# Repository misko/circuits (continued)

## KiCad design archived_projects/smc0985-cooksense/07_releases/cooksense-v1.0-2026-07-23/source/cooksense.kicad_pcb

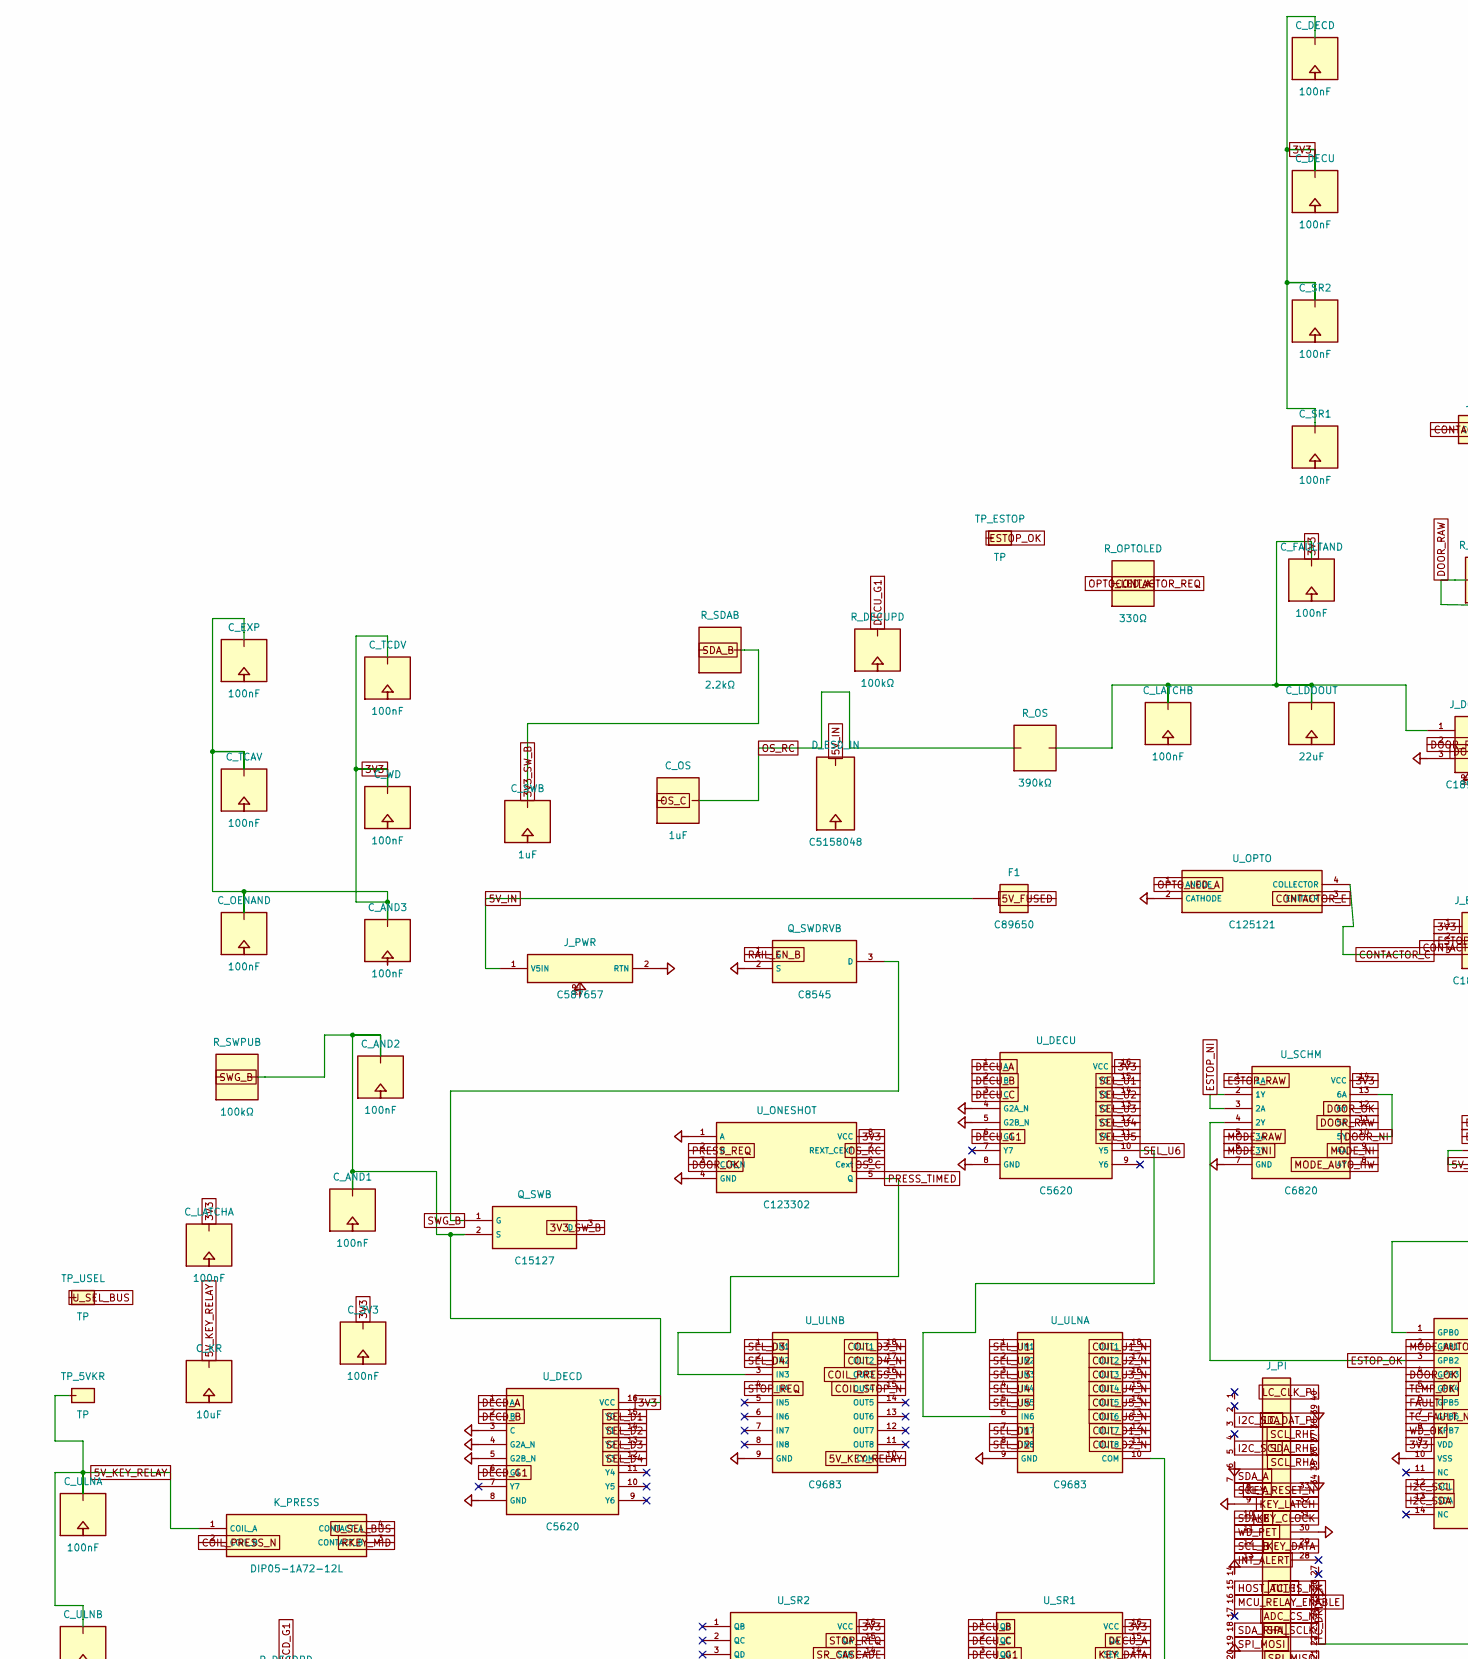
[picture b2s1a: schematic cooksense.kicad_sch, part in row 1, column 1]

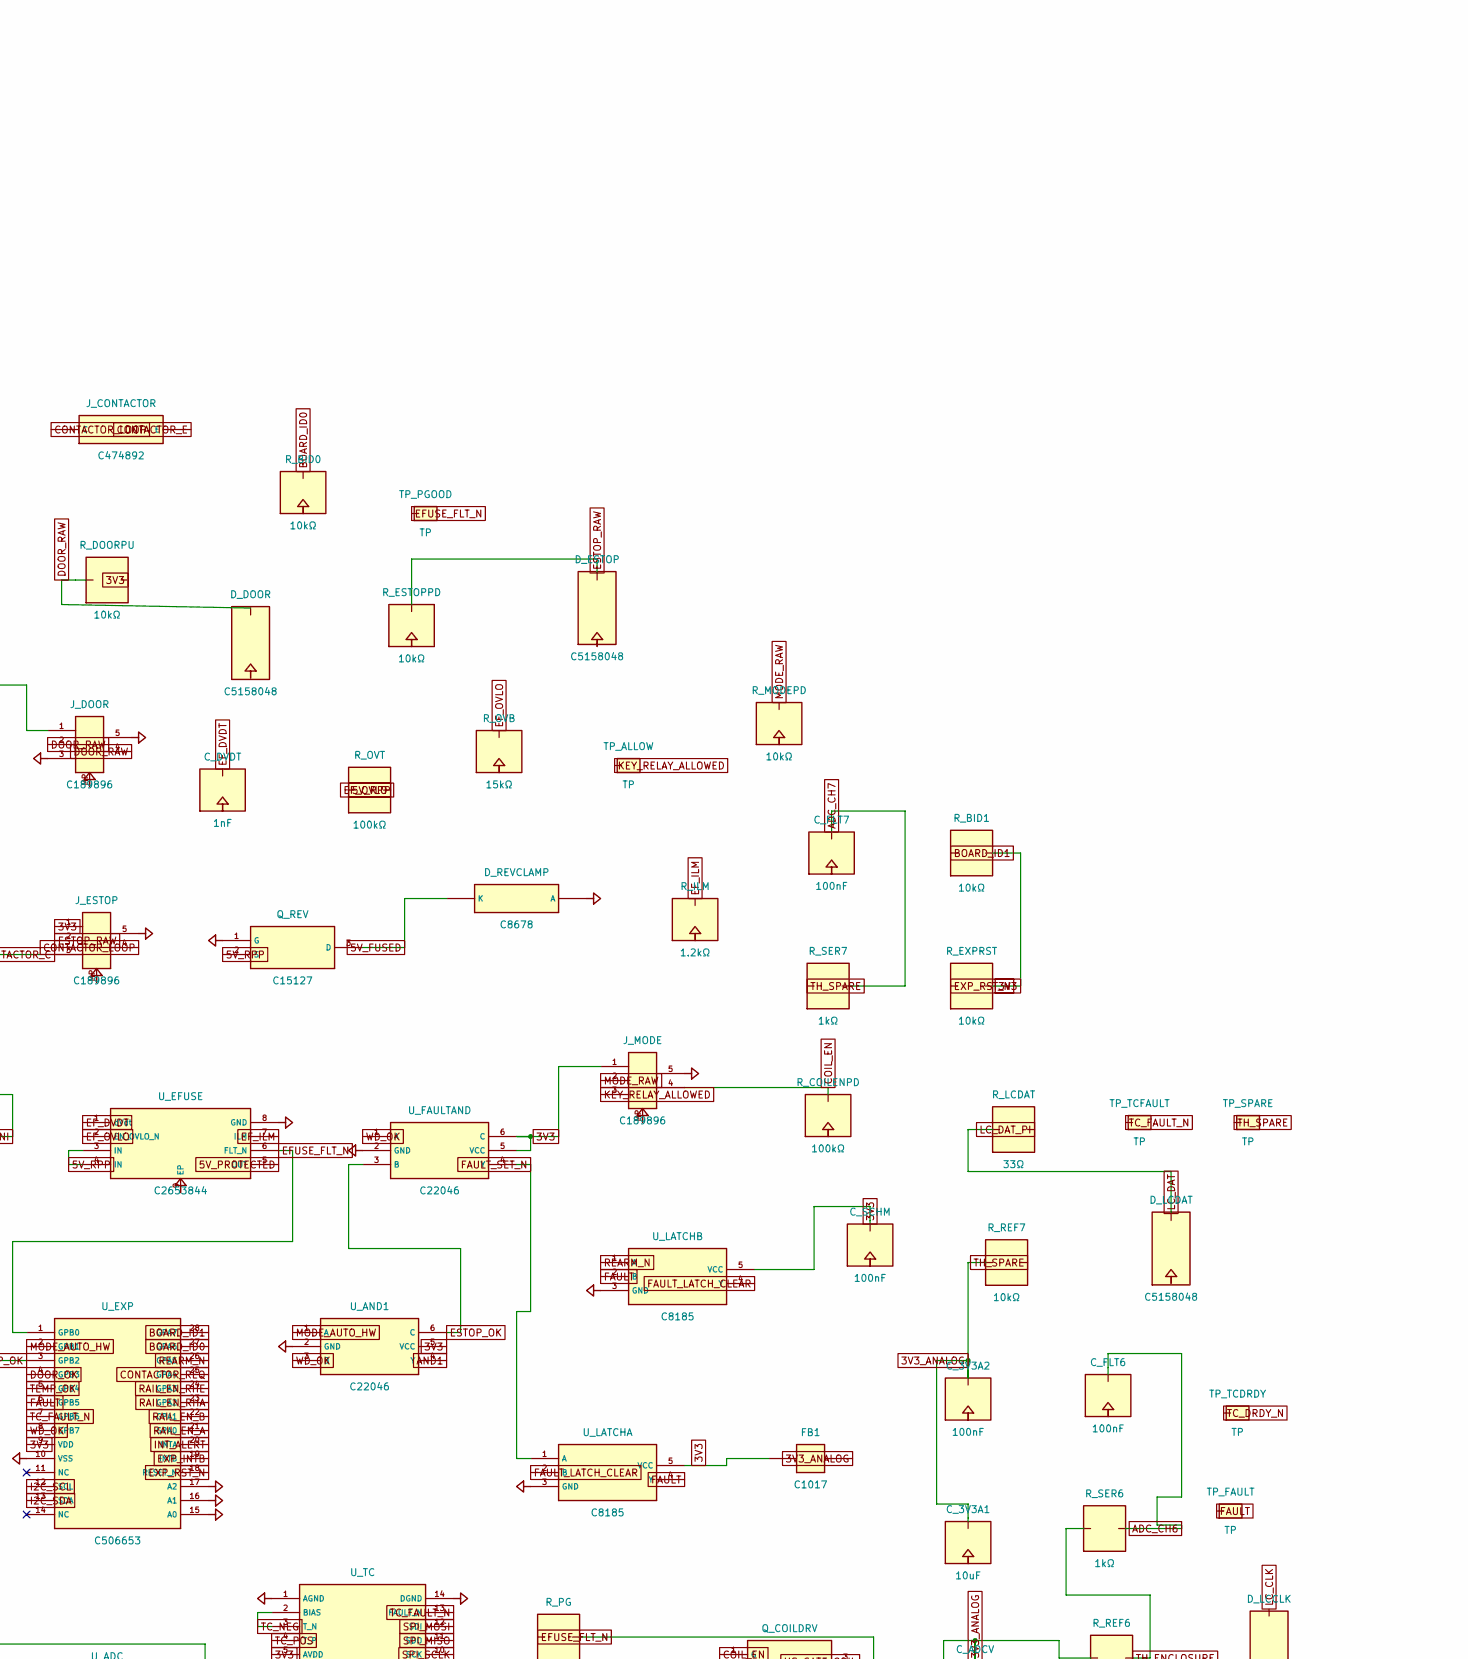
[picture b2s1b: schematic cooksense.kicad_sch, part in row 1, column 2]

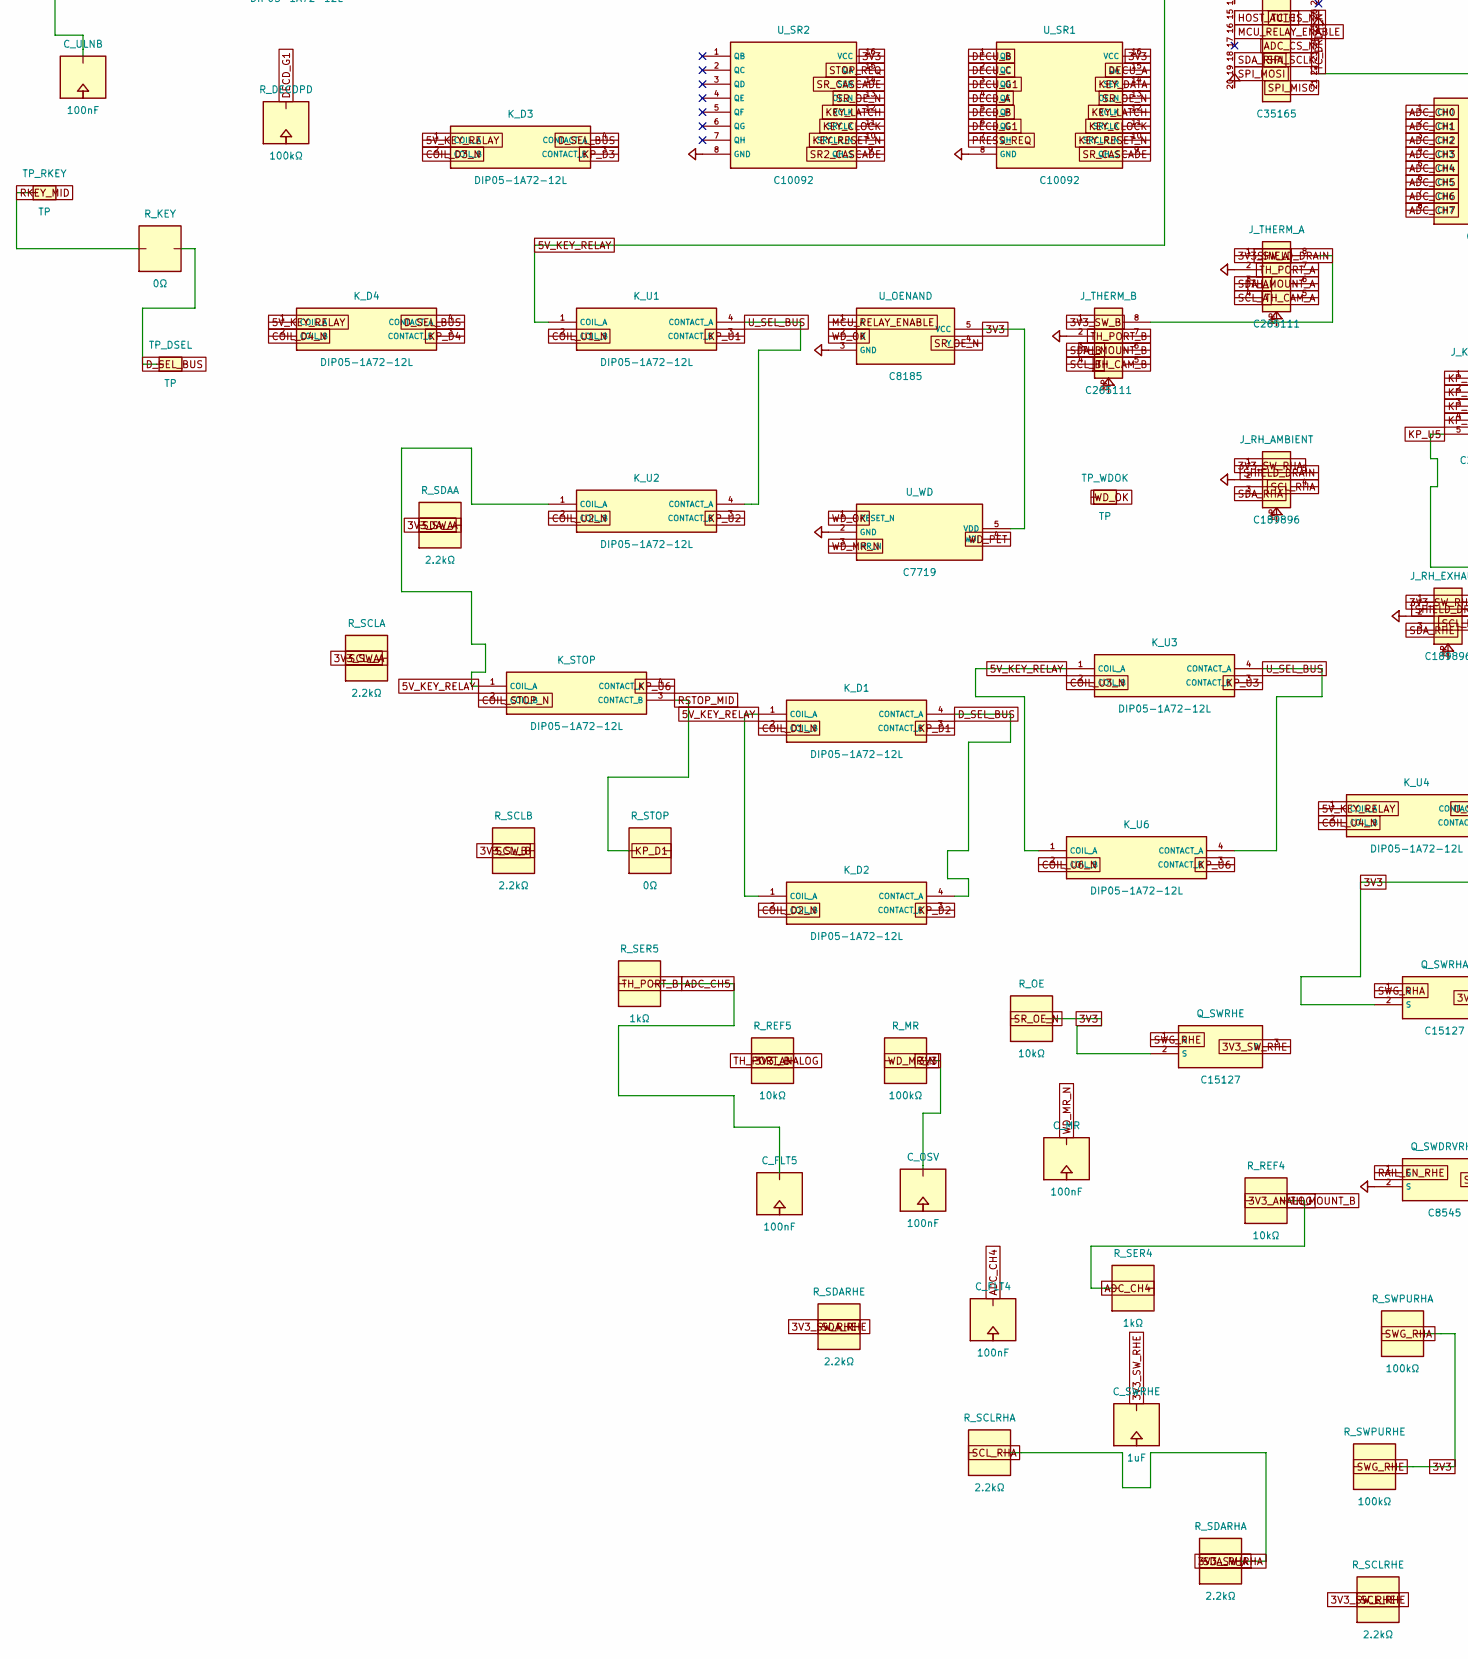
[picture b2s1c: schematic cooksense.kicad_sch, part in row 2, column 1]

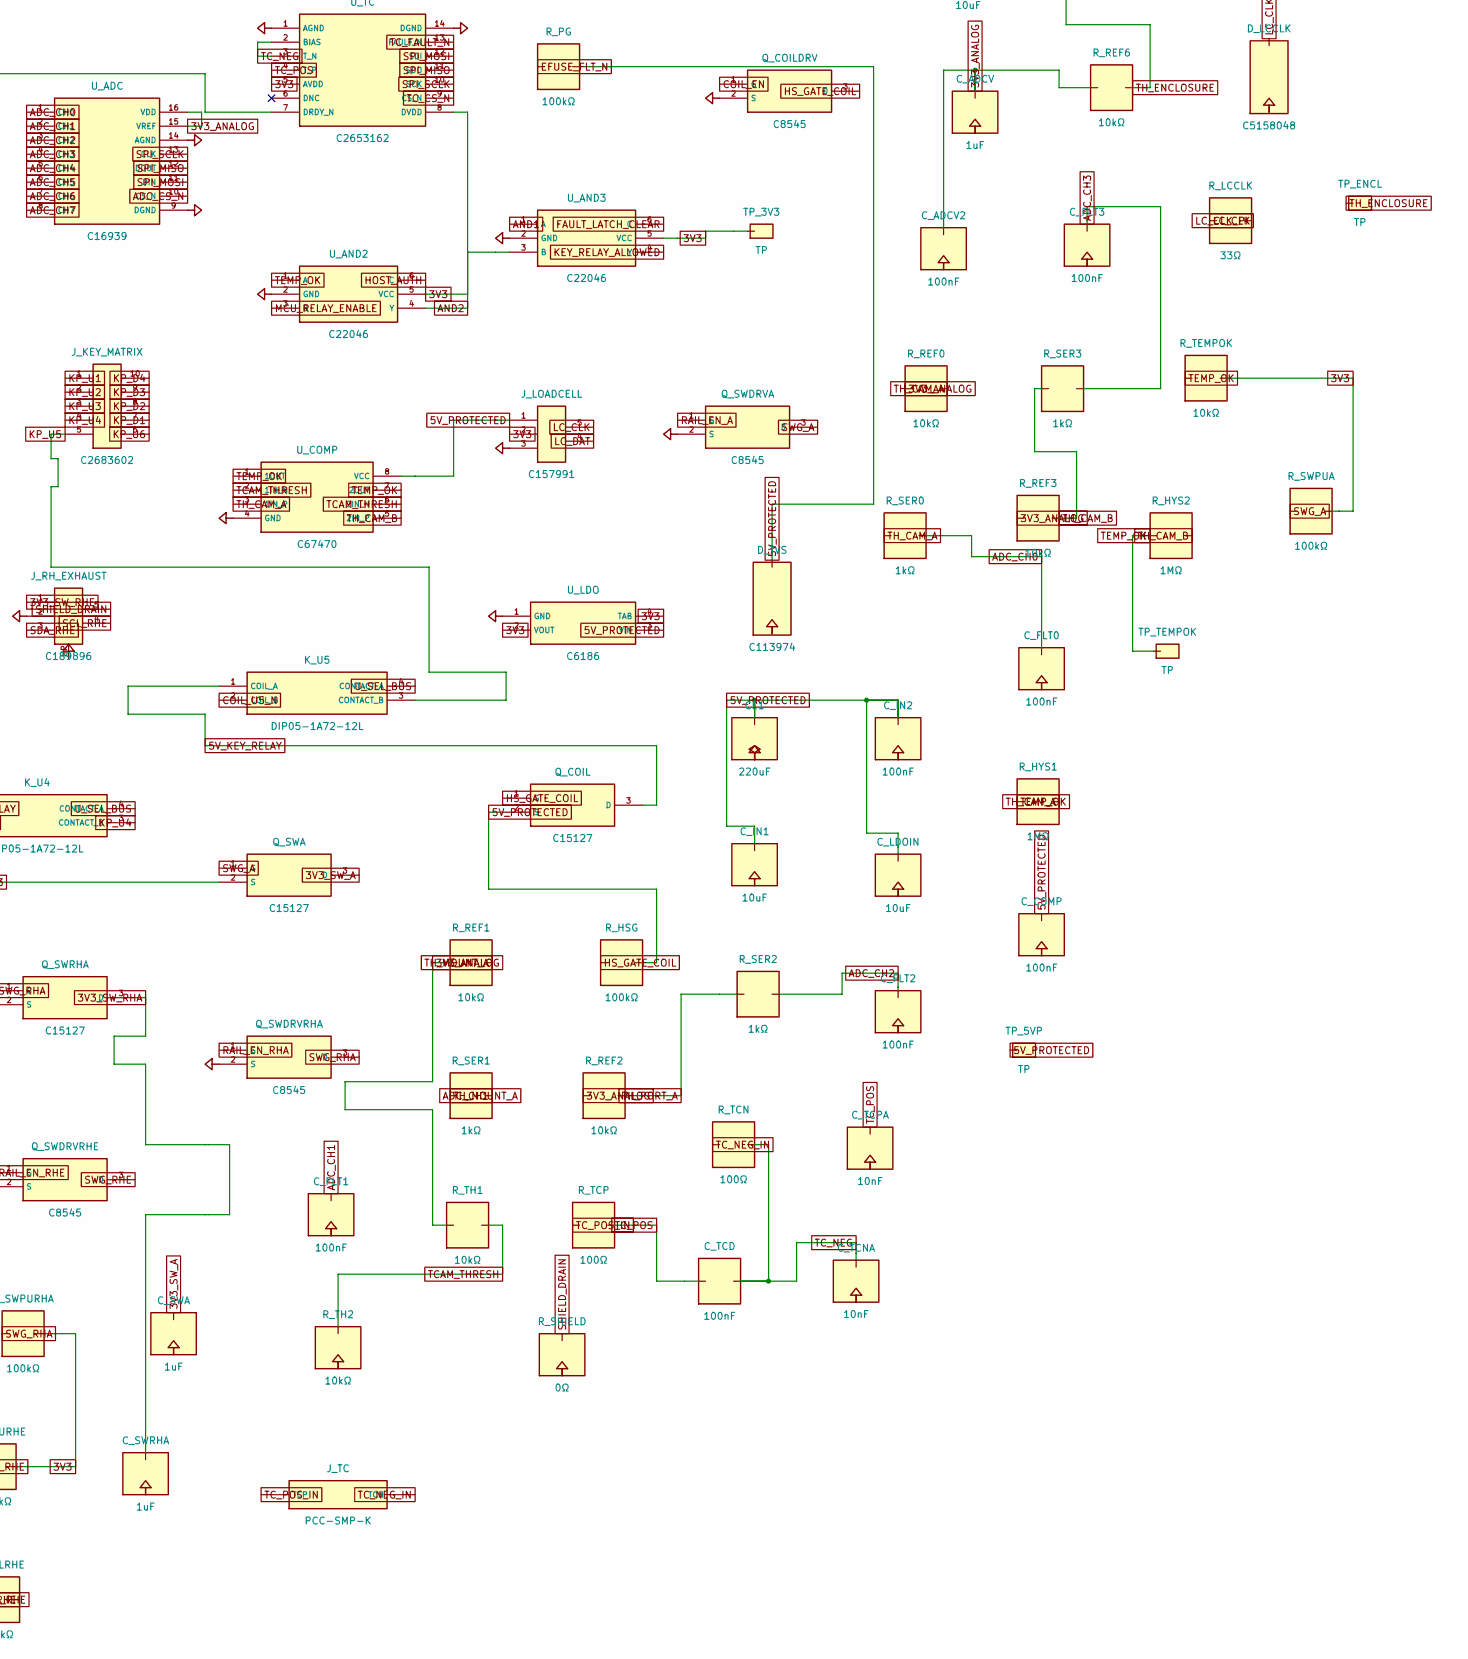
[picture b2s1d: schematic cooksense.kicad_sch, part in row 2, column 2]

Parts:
CE1: 220uF; CP_Elec_6.3x7.7
C_3V3, C_3V3A2: 100nF; C_0603_1608Metric
C_3V3A1: 10uF; C_0805_2012Metric
C_ADCV: 1uF; C_0603_1608Metric
C_ADCV2: 100nF; C_0402_1005Metric
C_AND1, C_AND2, C_AND3: 100nF; C_0402_1005Metric
C_COMP: 100nF; C_0402_1005Metric
C_DECD: 100nF; C_0402_1005Metric
C_DECU: 100nF; C_0402_1005Metric
C_DVDT: 1nF; C_0402_1005Metric
C_EXP: 100nF; C_0402_1005Metric
C_FAULTAND: 100nF; C_0402_1005Metric
C_FLT0, C_FLT1, C_FLT2, C_FLT3, C_FLT4, C_FLT5, C_FLT6, C_FLT7: 100nF; C_0402_1005Metric
C_IN1: 10uF; C_0805_2012Metric
C_IN2: 100nF; C_0603_1608Metric
C_KR: 10uF; C_0805_2012Metric
C_LATCHA: 100nF; C_0402_1005Metric
C_LATCHB: 100nF; C_0402_1005Metric
C_LDOIN: 10uF; C_0805_2012Metric
C_LDOOUT: 22uF; C_0805_2012Metric
C_MR: 100nF; C_0402_1005Metric
C_OENAND: 100nF; C_0402_1005Metric
C_OS: 1uF; C_0603_1608Metric
C_OSV: 100nF; C_0402_1005Metric
C_SCHM: 100nF; C_0402_1005Metric
C_SR1, C_SR2: 100nF; C_0402_1005Metric
C_SWA: 1uF; C_0603_1608Metric
C_SWB: 1uF; C_0603_1608Metric
C_SWRHA: 1uF; C_0603_1608Metric
C_SWRHE: 1uF; C_0603_1608Metric
C_TCAV: 100nF; C_0402_1005Metric
C_TCD: 100nF; C_0402_1005Metric
C_TCDV: 100nF; C_0402_1005Metric
C_TCNA: 10nF; C_0402_1005Metric
C_TCPA: 10nF; C_0402_1005Metric
C_ULNA: 100nF; C_0603_1608Metric
C_ULNB: 100nF; C_0603_1608Metric
C_WD: 100nF; C_0402_1005Metric
D_DOOR: C5158048; D_SOD-323
D_ESD_IN: C5158048; D_SOD-323
D_ESTOP: C5158048; D_SOD-323
D_LCCLK: C5158048; D_SOD-323
D_LCDAT: C5158048; D_SOD-323
D_REVCLAMP: C8678; D_SMA
D_TVS: C113974; D_SMB
F1: C89650; Fuse_1812_4532Metric
FB1: C1017; L_0805_2012Metric
J_CONTACTOR: C474892; TerminalBlock_KF350_2P
J_DOOR: C189896; JST_GH_SM05B-GHS-TB_1x05-1MP_P1.25mm_Horizontal
J_ESTOP: C189896; JST_GH_SM05B-GHS-TB_1x05-1MP_P1.25mm_Horizontal
J_KEY_MATRIX: C2683602; JST_GH_SM10B-GHS-TB_1x10-1MP_P1.25mm_Horizontal
J_LOADCELL: C157991; JST_XH_B5B-XH-A_1x05_P2.50mm_Vertical
J_MODE: C189896; JST_GH_SM05B-GHS-TB_1x05-1MP_P1.25mm_Horizontal
J_PI: C35165; PinSocket_2x20_P2.54mm_Vertical
J_PWR: C587657; Molex_Micro-Fit_3.0_43650-0224_1x02-1MP_P3.00mm_Vertical
J_RH_AMBIENT: C189896; JST_GH_SM05B-GHS-TB_1x05-1MP_P1.25mm_Horizontal
J_RH_EXHAUST: C189896; JST_GH_SM05B-GHS-TB_1x05-1MP_P1.25mm_Horizontal
J_TC: PCC-SMP-K; Omega_PCC-SMP-K_TypeK_PCpin
J_THERM_A: C265111; JST_GH_SM08B-GHS-TB_1x08-1MP_P1.25mm_Horizontal
J_THERM_B: C265111; JST_GH_SM08B-GHS-TB_1x08-1MP_P1.25mm_Horizontal
K_D1, K_D2, K_D3, K_D4: DIP05-1A72-12L; Relay_StandexDIP_1A_pinout12
K_PRESS: DIP05-1A72-12L; Relay_StandexDIP_1A_pinout12
K_STOP: DIP05-1A72-12L; Relay_StandexDIP_1A_pinout12
K_U1, K_U2, K_U3, K_U4, K_U5, K_U6: DIP05-1A72-12L; Relay_StandexDIP_1A_pinout12
Q_COIL: C15127; SOT-23
Q_COILDRV: C8545; SOT-23
Q_REV: C15127; SOT-23
Q_SWA: C15127; SOT-23
Q_SWB: C15127; SOT-23
Q_SWDRVA: C8545; SOT-23
Q_SWDRVB: C8545; SOT-23
Q_SWDRVRHA: C8545; SOT-23
Q_SWDRVRHE: C8545; SOT-23
Q_SWRHA: C15127; SOT-23
Q_SWRHE: C15127; SOT-23
R_BID0, R_BID1: 10kΩ; R_0402_1005Metric
R_COILENPD: 100kΩ; R_0402_1005Metric
R_DECDPD: 100kΩ; R_0402_1005Metric
R_DECUPD: 100kΩ; R_0402_1005Metric
R_DOORPU: 10kΩ; R_0402_1005Metric
R_ESTOPPD: 10kΩ; R_0402_1005Metric
R_EXPRST: 10kΩ; R_0402_1005Metric
R_HSG: 100kΩ; R_0402_1005Metric
R_HYS1, R_HYS2: 1MΩ; R_0402_1005Metric
R_ILM: 1.2kΩ; R_0402_1005Metric
R_KEY: 0Ω; R_1206_3216Metric
R_LCCLK: 33Ω; R_0402_1005Metric
R_LCDAT: 33Ω; R_0402_1005Metric
R_MODEPD: 10kΩ; R_0402_1005Metric
R_MR: 100kΩ; R_0402_1005Metric
R_OE: 10kΩ; R_0402_1005Metric
R_OPTOLED: 330Ω; R_0603_1608Metric
R_OS: 390kΩ; R_0402_1005Metric
R_OVB: 15kΩ; R_0402_1005Metric
R_OVT: 100kΩ; R_0402_1005Metric
R_PG: 100kΩ; R_0402_1005Metric
R_REF0, R_REF1, R_REF2, R_REF3, R_REF4, R_REF5, R_REF6, R_REF7: 10kΩ; R_0402_1005Metric
R_SCLA: 2.2kΩ; R_0402_1005Metric
R_SCLB: 2.2kΩ; R_0402_1005Metric
R_SCLRHA: 2.2kΩ; R_0402_1005Metric
R_SCLRHE: 2.2kΩ; R_0402_1005Metric
R_SDAA: 2.2kΩ; R_0402_1005Metric
R_SDAB: 2.2kΩ; R_0402_1005Metric
R_SDARHA: 2.2kΩ; R_0402_1005Metric
R_SDARHE: 2.2kΩ; R_0402_1005Metric
R_SER0, R_SER1, R_SER2, R_SER3, R_SER4, R_SER5, R_SER6, R_SER7: 1kΩ; R_0402_1005Metric
R_SHIELD: 0Ω; R_0603_1608Metric
R_STOP: 0Ω; R_1206_3216Metric
R_SWPUA: 100kΩ; R_0402_1005Metric
R_SWPUB: 100kΩ; R_0402_1005Metric
R_SWPURHA: 100kΩ; R_0402_1005Metric
R_SWPURHE: 100kΩ; R_0402_1005Metric
R_TCN: 100Ω; R_0402_1005Metric
R_TCP: 100Ω; R_0402_1005Metric
R_TEMPOK: 10kΩ; R_0402_1005Metric
R_TH1, R_TH2: 10kΩ; R_0402_1005Metric
TP_3V3, TP_5VKR, TP_5VP: TP; TestPoint_Pad_D1.5mm
TP_ALLOW: TP; TestPoint_Pad_D1.5mm
TP_DSEL: TP; TestPoint_Pad_D1.5mm
TP_ENCL: TP; TestPoint_Pad_D1.5mm
TP_ESTOP: TP; TestPoint_Pad_D1.5mm
TP_FAULT: TP; TestPoint_Pad_D1.5mm
TP_PGOOD: TP; TestPoint_Pad_D1.5mm
TP_RKEY: TP; TestPoint_Pad_D1.5mm
TP_SPARE: TP; TestPoint_Pad_D1.5mm
TP_TCDRDY: TP; TestPoint_Pad_D1.5mm
TP_TCFAULT: TP; TestPoint_Pad_D1.5mm
TP_TEMPOK: TP; TestPoint_Pad_D1.5mm
TP_USEL: TP; TestPoint_Pad_D1.5mm
TP_WDOK: TP; TestPoint_Pad_D1.5mm
U_ADC: C16939; SOIC-16_3.9x9.9mm_P1.27mm
U_AND1, U_AND2, U_AND3: C22046; SOT-23-6
U_COMP: C67470; SOIC-8_3.9x4.9mm_P1.27mm
U_DECD: C5620; SOIC-16_3.9x9.9mm_P1.27mm
U_DECU: C5620; SOIC-16_3.9x9.9mm_P1.27mm
U_EFUSE: C2653844; Texas_DSG0008A_WSON-8-1EP_2x2mm_P0.5mm_EP0.9x1.6mm
U_EXP: C506653; SSOP-28_5.3x10.2mm_P0.65mm
U_FAULTAND: C22046; SOT-23-6
U_LATCHA: C8185; SOT-353_SC-70-5
U_LATCHB: C8185; SOT-353_SC-70-5
U_LDO: C6186; SOT-223
U_OENAND: C8185; SOT-353_SC-70-5
U_ONESHOT: C123302; SSOP-8_2.95x2.8mm_P0.65mm
U_OPTO: C125121; SMDIP-4_W9.53mm
U_SCHM: C6820; SOIC-14_3.9x8.7mm_P1.27mm
U_SR1, U_SR2: C10092; SOIC-16_3.9x9.9mm_P1.27mm
U_TC: C2653162; TSSOP-14_4.4x5mm_P0.65mm
U_ULNA: C9683; SOIC-18W_7.5x11.6mm_P1.27mm
U_ULNB: C9683; SOIC-18W_7.5x11.6mm_P1.27mm
U_WD: C7719; SOT-23-5

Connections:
3V3: C_3V3.1, C_AND1.1, C_AND2.1, C_AND3.1, C_DECD.1, C_DECU.1, C_EXP.1, C_FAULTAND.1, C_LATCHA.1, C_LATCHB.1, C_LDOOUT.1, C_OENAND.1, C_OSV.1, C_SCHM.1, C_SR1.1, C_SR2.1, C_TCAV.1, C_TCDV.1, C_WD.1, FB1.1, J_DOOR.1, J_ESTOP.1, J_LOADCELL.2, J_MODE.1, Q_SWA.2 (S), Q_SWB.2 (S), Q_SWRHA.2 (S), Q_SWRHE.2 (S), R_BID1.2, R_DOORPU.2, R_EXPRST.2, R_MR.2, R_OE.2, R_OS.2, R_SWPUA.2, R_SWPUB.2, R_SWPURHA.2, R_SWPURHE.2, R_TEMPOK.2, TP_3V3.1, U_AND1.5 (VCC), U_AND2.5 (VCC), U_AND3.5 (VCC), U_DECD.16 (VCC), U_DECU.16 (VCC), U_EXP.9 (VDD), U_FAULTAND.5 (VCC), U_FAULTAND.6 (C), U_LATCHA.5 (VCC), U_LATCHB.5 (VCC), U_LDO.2 (VOUT), U_LDO.4 (TAB), U_OENAND.5 (VCC), U_ONESHOT.8 (VCC), U_SCHM.14 (VCC), U_SR1.16 (VCC), U_SR2.16 (VCC), U_TC.5 (AVDD), U_TC.8 (DVDD), U_WD.5 (VDD)
3V3_ANALOG: C_3V3A1.1, C_3V3A2.1, C_ADCV.1, C_ADCV2.1, FB1.2, R_REF0.1, R_REF1.1, R_REF2.1, R_REF3.1, R_REF4.1, R_REF5.1, R_REF6.1, R_REF7.1, R_TH1.1, U_ADC.15 (VREF), U_ADC.16 (VDD)
3V3_SW_A: C_SWA.1, J_THERM_A.1, Q_SWA.3 (D), R_SCLA.2, R_SDAA.2
3V3_SW_B: C_SWB.1, J_THERM_B.1, Q_SWB.3 (D), R_SCLB.2, R_SDAB.2
3V3_SW_RHA: C_SWRHA.1, J_RH_AMBIENT.1, Q_SWRHA.3 (D), R_SCLRHA.2, R_SDARHA.2
3V3_SW_RHE: C_SWRHE.1, J_RH_EXHAUST.1, Q_SWRHE.3 (D), R_SCLRHE.2, R_SDARHE.2
5V_FUSED: D_REVCLAMP.1 (K), F1.2, Q_REV.3 (D)
5V_IN: D_ESD_IN.1, F1.1, J_PWR.1 (V5IN)
5V_KEY_RELAY: C_KR.1, C_ULNA.1, C_ULNB.1, K_D1.1 (COIL_A), K_D2.1 (COIL_A), K_D3.1 (COIL_A), K_D4.1 (COIL_A), K_PRESS.1 (COIL_A), K_STOP.1 (COIL_A), K_U1.1 (COIL_A), K_U2.1 (COIL_A), K_U3.1 (COIL_A), K_U4.1 (COIL_A), K_U5.1 (COIL_A), K_U6.1 (COIL_A), Q_COIL.3 (D), TP_5VKR.1, U_ULNA.10 (COM), U_ULNB.10 (COM)
5V_PROTECTED: CE1.1, C_COMP.1, C_IN1.1, C_IN2.1, C_LDOIN.1, D_TVS.1, J_LOADCELL.1, Q_COIL.2 (S), R_HSG.2, R_PG.2, TP_5VP.1, U_COMP.8 (VCC), U_EFUSE.5 (OUT), U_LDO.3 (VIN)
5V_RPP: Q_REV.2 (S), R_OVT.1, U_EFUSE.3 (IN), U_EFUSE.4 (IN)
ADC_CH0: C_FLT0.1, R_SER0.2, U_ADC.1 (CH0)
ADC_CH1: C_FLT1.1, R_SER1.2, U_ADC.2 (CH1)
ADC_CH2: C_FLT2.1, R_SER2.2, U_ADC.3 (CH2)
ADC_CH3: C_FLT3.1, R_SER3.2, U_ADC.4 (CH3)
ADC_CH4: C_FLT4.1, R_SER4.2, U_ADC.5 (CH4)
ADC_CH5: C_FLT5.1, R_SER5.2, U_ADC.6 (CH5)
ADC_CH6: C_FLT6.1, R_SER6.2, U_ADC.7 (CH6)
ADC_CH7: C_FLT7.1, R_SER7.2, U_ADC.8 (CH7)
ADC_CS_N: J_PI.24, U_ADC.10 (CS_N)
AND1: U_AND1.4 (Y), U_AND3.1 (A)
AND2: U_AND2.4 (Y), U_AND3.3 (B)
BOARD_ID0: R_BID0.1, U_EXP.27 (GPA6)
BOARD_ID1: R_BID1.1, U_EXP.28 (GPA7)
COIL_D1_N: K_D1.2 (COIL_B), U_ULNA.12 (OUT7)
COIL_D2_N: K_D2.2 (COIL_B), U_ULNA.11 (OUT8)
COIL_D3_N: K_D3.2 (COIL_B), U_ULNB.18 (OUT1)
COIL_D4_N: K_D4.2 (COIL_B), U_ULNB.17 (OUT2)
COIL_EN: J_MODE.4, Q_COILDRV.1 (G), R_COILENPD.1
COIL_PRESS_N: K_PRESS.2 (COIL_B), U_ULNB.16 (OUT3)
COIL_STOP_N: K_STOP.2 (COIL_B), U_ULNB.15 (OUT4)
COIL_U1_N: K_U1.2 (COIL_B), U_ULNA.18 (OUT1)
COIL_U2_N: K_U2.2 (COIL_B), U_ULNA.17 (OUT2)
COIL_U3_N: K_U3.2 (COIL_B), U_ULNA.16 (OUT3)
COIL_U4_N: K_U4.2 (COIL_B), U_ULNA.15 (OUT4)
COIL_U5_N: K_U5.2 (COIL_B), U_ULNA.14 (OUT5)
COIL_U6_N: K_U6.2 (COIL_B), U_ULNA.13 (OUT6)
CONTACTOR_C: J_ESTOP.3, U_OPTO.4 (COLLECTOR)
CONTACTOR_E: J_CONTACTOR.2 (E), U_OPTO.3 (EMITTER)
CONTACTOR_LOOP: J_CONTACTOR.1 (C), J_ESTOP.4
CONTACTOR_REQ: R_OPTOLED.1, U_EXP.25 (GPA4)
DECD_A: U_DECD.1 (A), U_SR1.4 (QE)
DECD_B: U_DECD.2 (B), U_SR1.5 (QF)
DECD_G1: R_DECDPD.1, U_DECD.6 (G1), U_SR1.6 (QG)
DECU_A: U_DECU.1 (A), U_SR1.15 (QA)
DECU_B: U_DECU.2 (B), U_SR1.1 (QB)
DECU_C: U_DECU.3 (C), U_SR1.2 (QC)
DECU_G1: R_DECUPD.1, U_DECU.6 (G1), U_SR1.3 (QD)
DOOR_NI: U_SCHM.10 (5Y), U_SCHM.13 (6A)
DOOR_OK: U_EXP.4 (GPB3), U_ONESHOT.3 (CLR_N), U_SCHM.12 (6Y)
DOOR_RAW: D_DOOR.1, J_DOOR.2, J_DOOR.4, R_DOORPU.1, U_SCHM.11 (5A)
D_SEL_BUS: K_D1.4 (CONTACT_A), K_D2.4 (CONTACT_A), K_D3.4 (CONTACT_A), K_D4.4 (CONTACT_A), R_KEY.2, TP_DSEL.1
EFUSE_FLT_N: R_PG.1, TP_PGOOD.1, U_EFUSE.6 (FLT_N), U_EXP.1 (GPB0)
EF_DVDT: C_DVDT.1, U_EFUSE.1 (dVdt)
EF_ILM: R_ILM.1, U_EFUSE.7 (ILM)
EF_OVLO: R_OVB.1, R_OVT.2, U_EFUSE.2 (EN_OVLO_N)
ESTOP_NI: U_SCHM.2 (1Y), U_SCHM.3 (2A)
ESTOP_OK: TP_ESTOP.1, U_AND1.6 (C), U_EXP.3 (GPB2), U_FAULTAND.3 (B), U_SCHM.4 (2Y)
ESTOP_RAW: D_ESTOP.1, J_ESTOP.2, R_ESTOPPD.1, U_SCHM.1 (1A)
EXP_INTB: U_EXP.19 (INTB)
EXP_RST_N: R_EXPRST.1, U_EXP.18 (RESET_N)
FAULT: TP_FAULT.1, U_EXP.6 (GPB5), U_LATCHA.4 (Y), U_LATCHB.2 (B)
FAULT_LATCH_CLEAR: U_AND3.6 (C), U_LATCHA.2 (B), U_LATCHB.4 (Y)
FAULT_SET_N: U_FAULTAND.4 (Y), U_LATCHA.1 (A)
GND: CE1.2, C_3V3.2, C_3V3A1.2, C_3V3A2.2, C_ADCV.2, C_ADCV2.2, C_AND1.2, C_AND2.2, C_AND3.2, C_COMP.2, C_DECD.2, C_DECU.2, C_DVDT.2, C_EXP.2, C_FAULTAND.2, C_FLT0.2, C_FLT1.2, C_FLT2.2, C_FLT3.2, C_FLT4.2, C_FLT5.2, C_FLT6.2, C_FLT7.2, C_IN1.2, C_IN2.2, C_KR.2, C_LATCHA.2, C_LATCHB.2, C_LDOIN.2, C_LDOOUT.2, C_MR.2, C_OENAND.2, C_OSV.2, C_SCHM.2, C_SR1.2, C_SR2.2, C_SWA.2, C_SWB.2, C_SWRHA.2, C_SWRHE.2, C_TCAV.2, C_TCDV.2, C_TCNA.2, C_TCPA.2, C_ULNA.2, C_ULNB.2, C_WD.2, D_DOOR.2, D_ESD_IN.2, D_ESTOP.2, D_LCCLK.2, D_LCDAT.2, D_REVCLAMP.2 (A), D_TVS.2, J_DOOR.3, J_DOOR.5, J_DOOR.MP, J_ESTOP.5, J_ESTOP.MP, J_LOADCELL.3, J_MODE.5, J_MODE.MP, J_PI.6, J_PI.9, J_PI.14, J_PI.20, J_PI.25, J_PI.30, J_PI.34, J_PI.39, J_PWR.2 (RTN), J_PWR.MP, J_RH_AMBIENT.2, J_RH_AMBIENT.MP, J_RH_EXHAUST.2, J_RH_EXHAUST.MP, J_THERM_A.2, J_THERM_A.MP, J_THERM_B.2, J_THERM_B.MP, Q_COILDRV.2 (S), Q_REV.1 (G), Q_SWDRVA.2 (S), Q_SWDRVB.2 (S), Q_SWDRVRHA.2 (S), Q_SWDRVRHE.2 (S), R_BID0.2, R_COILENPD.2, R_DECDPD.2, R_DECUPD.2, R_ESTOPPD.2, R_ILM.2, R_MODEPD.2, R_OVB.2, R_SHIELD.2, R_TH2.2, U_ADC.9 (DGND), U_ADC.14 (AGND), U_AND1.2 (GND), U_AND2.2 (GND), U_AND3.2 (GND), U_COMP.4 (GND), U_DECD.3 (C), U_DECD.4 (G2A_N), U_DECD.5 (G2B_N), U_DECD.8 (GND), U_DECU.4 (G2A_N), U_DECU.5 (G2B_N), U_DECU.8 (GND), U_EFUSE.8 (GND), U_EFUSE.9 (EP), U_EXP.10 (VSS), U_EXP.15 (A0), U_EXP.16 (A1), U_EXP.17 (A2), U_FAULTAND.2 (GND), U_LATCHA.3 (GND), U_LATCHB.3 (GND), U_LDO.1 (GND), U_OENAND.3 (GND), U_ONESHOT.1 (A), U_ONESHOT.4 (GND), U_OPTO.2 (CATHODE), U_SCHM.7 (GND), U_SR1.8 (GND), U_SR2.8 (GND), U_TC.1 (AGND), U_TC.14 (DGND), U_ULNA.9 (GND), U_ULNB.9 (GND), U_WD.2 (GND)
HOST_AUTH: J_PI.15, U_AND2.6 (C)
HS_GATE_COIL: Q_COIL.1 (G), Q_COILDRV.3 (D), R_HSG.1
I2C_SCL: J_PI.5, U_EXP.12 (SCL)
I2C_SDA: J_PI.3, U_EXP.13 (SDA)
INT_ALERT: J_PI.13, U_EXP.20 (INTA)
KEY_CLOCK: J_PI.31, U_SR1.11 (SRCLK), U_SR2.11 (SRCLK)
KEY_DATA: J_PI.29, U_SR1.14 (SER)
KEY_LATCH: J_PI.32, U_SR1.12 (RCLK), U_SR2.12 (RCLK)
KEY_RELAY_ALLOWED: J_MODE.3, TP_ALLOW.1, U_AND3.4 (Y)
KEY_RESET_N: J_PI.33, U_SR1.10 (SRCLR_N), U_SR2.10 (SRCLR_N)
KP_D1: J_KEY_MATRIX.7, K_D1.3 (CONTACT_B), R_STOP.2
KP_D2: J_KEY_MATRIX.8, K_D2.3 (CONTACT_B)
KP_D3: J_KEY_MATRIX.9, K_D3.3 (CONTACT_B)
KP_D4: J_KEY_MATRIX.10, K_D4.3 (CONTACT_B)
KP_U1: J_KEY_MATRIX.1, K_U1.3 (CONTACT_B)
KP_U2: J_KEY_MATRIX.2, K_U2.3 (CONTACT_B)
KP_U3: J_KEY_MATRIX.3, K_U3.3 (CONTACT_B)
KP_U4: J_KEY_MATRIX.4, K_U4.3 (CONTACT_B)
KP_U5: J_KEY_MATRIX.5, K_U5.3 (CONTACT_B)
KP_U6: J_KEY_MATRIX.6, K_STOP.4 (CONTACT_A), K_U6.3 (CONTACT_B)
LC_CLK: D_LCCLK.1, J_LOADCELL.5, R_LCCLK.1
LC_CLK_PI: J_PI.40, R_LCCLK.2
LC_DAT: D_LCDAT.1, J_LOADCELL.4, R_LCDAT.1
LC_DAT_PI: J_PI.38, R_LCDAT.2
MCU_RELAY_ENABLE: J_PI.16, U_AND2.3 (B), U_OENAND.1 (A)
MODE_AUTO_HW: U_AND1.1 (A), U_EXP.2 (GPB1), U_SCHM.8 (4Y)
MODE_NI: U_SCHM.6 (3Y), U_SCHM.9 (4A)
MODE_RAW: J_MODE.2, R_MODEPD.1, U_SCHM.5 (3A)
OPTO_LED_A: R_OPTOLED.2, U_OPTO.1 (ANODE)
OS_C: C_OS.1, U_ONESHOT.6 (Cext)
OS_RC: C_OS.2, R_OS.1, U_ONESHOT.7 (REXT_CEXT)
PRESS_REQ: U_ONESHOT.2 (B), U_SR1.7 (QH)
PRESS_TIMED: U_ONESHOT.5 (Q), U_ULNB.3 (IN3)
RAIL_EN_A: Q_SWDRVA.1 (G), U_EXP.21 (GPA0)
RAIL_EN_B: Q_SWDRVB.1 (G), U_EXP.22 (GPA1)
RAIL_EN_RHA: Q_SWDRVRHA.1 (G), U_EXP.23 (GPA2)
RAIL_EN_RHE: Q_SWDRVRHE.1 (G), U_EXP.24 (GPA3)
REARM_N: U_EXP.26 (GPA5), U_LATCHB.1 (A)
RKEY_MID: K_PRESS.3 (CONTACT_B), R_KEY.1, TP_RKEY.1
RSTOP_MID: K_STOP.3 (CONTACT_B), R_STOP.1
SCL_A: J_PI.8, J_THERM_A.4, R_SCLA.1
SCL_B: J_PI.12, J_THERM_B.4, R_SCLB.1
SCL_RHA: J_PI.35, J_RH_AMBIENT.4, R_SCLRHA.1
SCL_RHE: J_PI.37, J_RH_EXHAUST.4, R_SCLRHE.1
SDA_A: J_PI.7, J_THERM_A.3, R_SDAA.1
SDA_B: J_PI.10, J_THERM_B.3, R_SDAB.1
SDA_RHA: J_PI.18, J_RH_AMBIENT.3, R_SDARHA.1
SDA_RHE: J_PI.36, J_RH_EXHAUST.3, R_SDARHE.1
SEL_D1: U_DECD.15 (Y0), U_ULNA.7 (IN7)
SEL_D2: U_DECD.14 (Y1), U_ULNA.8 (IN8)
SEL_D3: U_DECD.13 (Y2), U_ULNB.1 (IN1)
SEL_D4: U_DECD.12 (Y3), U_ULNB.2 (IN2)
SEL_U1: U_DECU.15 (Y0), U_ULNA.1 (IN1)
SEL_U2: U_DECU.14 (Y1), U_ULNA.2 (IN2)
SEL_U3: U_DECU.13 (Y2), U_ULNA.3 (IN3)
SEL_U4: U_DECU.12 (Y3), U_ULNA.4 (IN4)
SEL_U5: U_DECU.11 (Y4), U_ULNA.5 (IN5)
SEL_U6: U_DECU.10 (Y5), U_ULNA.6 (IN6)
SHIELD_DRAIN: J_RH_AMBIENT.5, J_RH_EXHAUST.5, J_THERM_A.8, J_THERM_B.8, R_SHIELD.1
SPI_MISO: J_PI.21, U_ADC.12 (DOUT), U_TC.11 (SDO)
SPI_MOSI: J_PI.19, U_ADC.11 (DIN), U_TC.12 (SDI)
SPI_SCLK: J_PI.23, U_ADC.13 (CLK), U_TC.10 (SCK)
SR2_CASCADE: U_SR2.9 (QH_S)
SR_CASCADE: U_SR1.9 (QH_S), U_SR2.14 (SER)
SR_OE_N: R_OE.1, U_OENAND.4 (Y), U_SR1.13 (OE_N), U_SR2.13 (OE_N)
STOP_REQ: U_SR2.15 (QA), U_ULNB.4 (IN4)
SWG_A: Q_SWA.1 (G), Q_SWDRVA.3 (D), R_SWPUA.1
SWG_B: Q_SWB.1 (G), Q_SWDRVB.3 (D), R_SWPUB.1
SWG_RHA: Q_SWDRVRHA.3 (D), Q_SWRHA.1 (G), R_SWPURHA.1
SWG_RHE: Q_SWDRVRHE.3 (D), Q_SWRHE.1 (G), R_SWPURHE.1
TCAM_THRESH: R_TH1.2, R_TH2.1, U_COMP.2 (1IN_N), U_COMP.6 (2IN_N)
TC_CS_N: J_PI.26, U_TC.9 (CS_N)
TC_DRDY_N: J_PI.22, TP_TCDRDY.1, U_TC.7 (DRDY_N)
TC_FAULT_N: TP_TCFAULT.1, U_EXP.7 (GPB6), U_TC.13 (FAULT_N)
TC_NEG: C_TCD.2, C_TCNA.1, R_TCN.2, U_TC.2 (BIAS), U_TC.3 (T_N)
TC_NEG_IN: J_TC.2 (TCN), R_TCN.1
TC_POS: C_TCD.1, C_TCPA.1, R_TCP.2, U_TC.4 (T_P)
TC_POS_IN: J_TC.1 (TCP), R_TCP.1
TEMP_OK: R_HYS1.1, R_HYS2.1, R_TEMPOK.1, TP_TEMPOK.1, U_AND2.1 (A), U_COMP.1 (1OUT), U_COMP.7 (2OUT), U_EXP.5 (GPB4)
TH_CAM_A: J_THERM_A.5, R_HYS1.2, R_REF0.2, R_SER0.1, U_COMP.3 (1IN_P)
TH_CAM_B: J_THERM_B.5, R_HYS2.2, R_REF3.2, R_SER3.1, U_COMP.5 (2IN_P)
TH_ENCLOSURE: R_REF6.2, R_SER6.1, TP_ENCL.1
TH_MOUNT_A: J_THERM_A.6, R_REF1.2, R_SER1.1
TH_MOUNT_B: J_THERM_B.6, R_REF4.2, R_SER4.1
TH_PORT_A: J_THERM_A.7, R_REF2.2, R_SER2.1
TH_PORT_B: J_THERM_B.7, R_REF5.2, R_SER5.1
TH_SPARE: R_REF7.2, R_SER7.1, TP_SPARE.1
U_SEL_BUS: K_PRESS.4 (CONTACT_A), K_U1.4 (CONTACT_A), K_U2.4 (CONTACT_A), K_U3.4 (CONTACT_A), K_U4.4 (CONTACT_A), K_U5.4 (CONTACT_A), K_U6.4 (CONTACT_A), TP_USEL.1
WD_MR_N: C_MR.1, R_MR.1, U_WD.3 (MR_N)
WD_OK: TP_WDOK.1, U_AND1.3 (B), U_EXP.8 (GPB7), U_FAULTAND.1 (A), U_OENAND.2 (B), U_WD.1 (RESET_N)
WD_PET: J_PI.11, U_WD.4 (WDI)

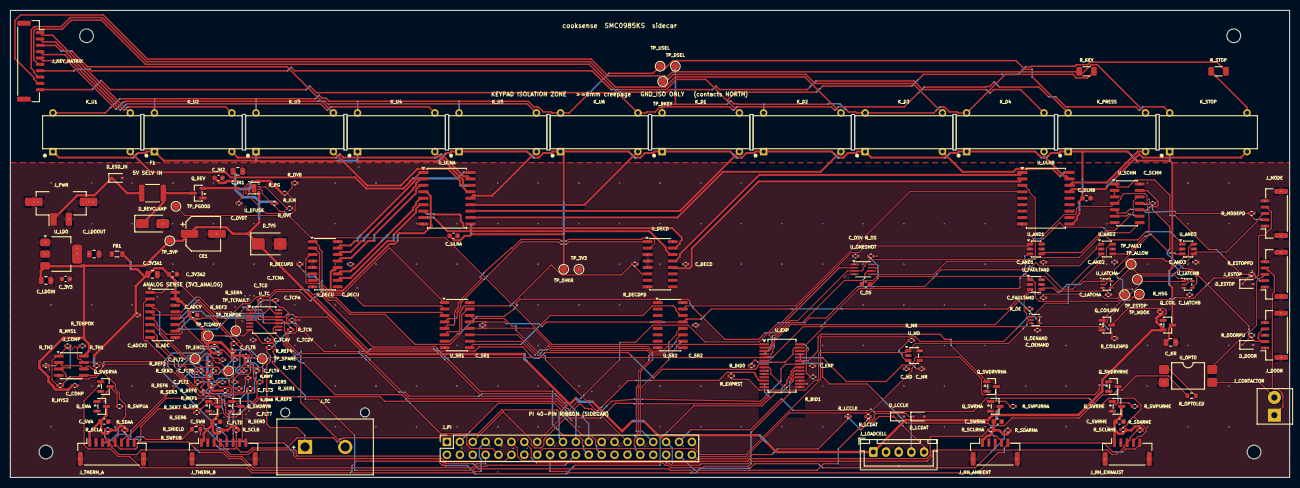
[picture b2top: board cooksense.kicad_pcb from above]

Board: 4 copper layers, 252.0 x 92.0 mm, 195 parts (0 on the bottom side), 154 nets.

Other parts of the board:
H1, H2, H3, H4: MountingHole_2.7mm_M2.5_ISO14580
